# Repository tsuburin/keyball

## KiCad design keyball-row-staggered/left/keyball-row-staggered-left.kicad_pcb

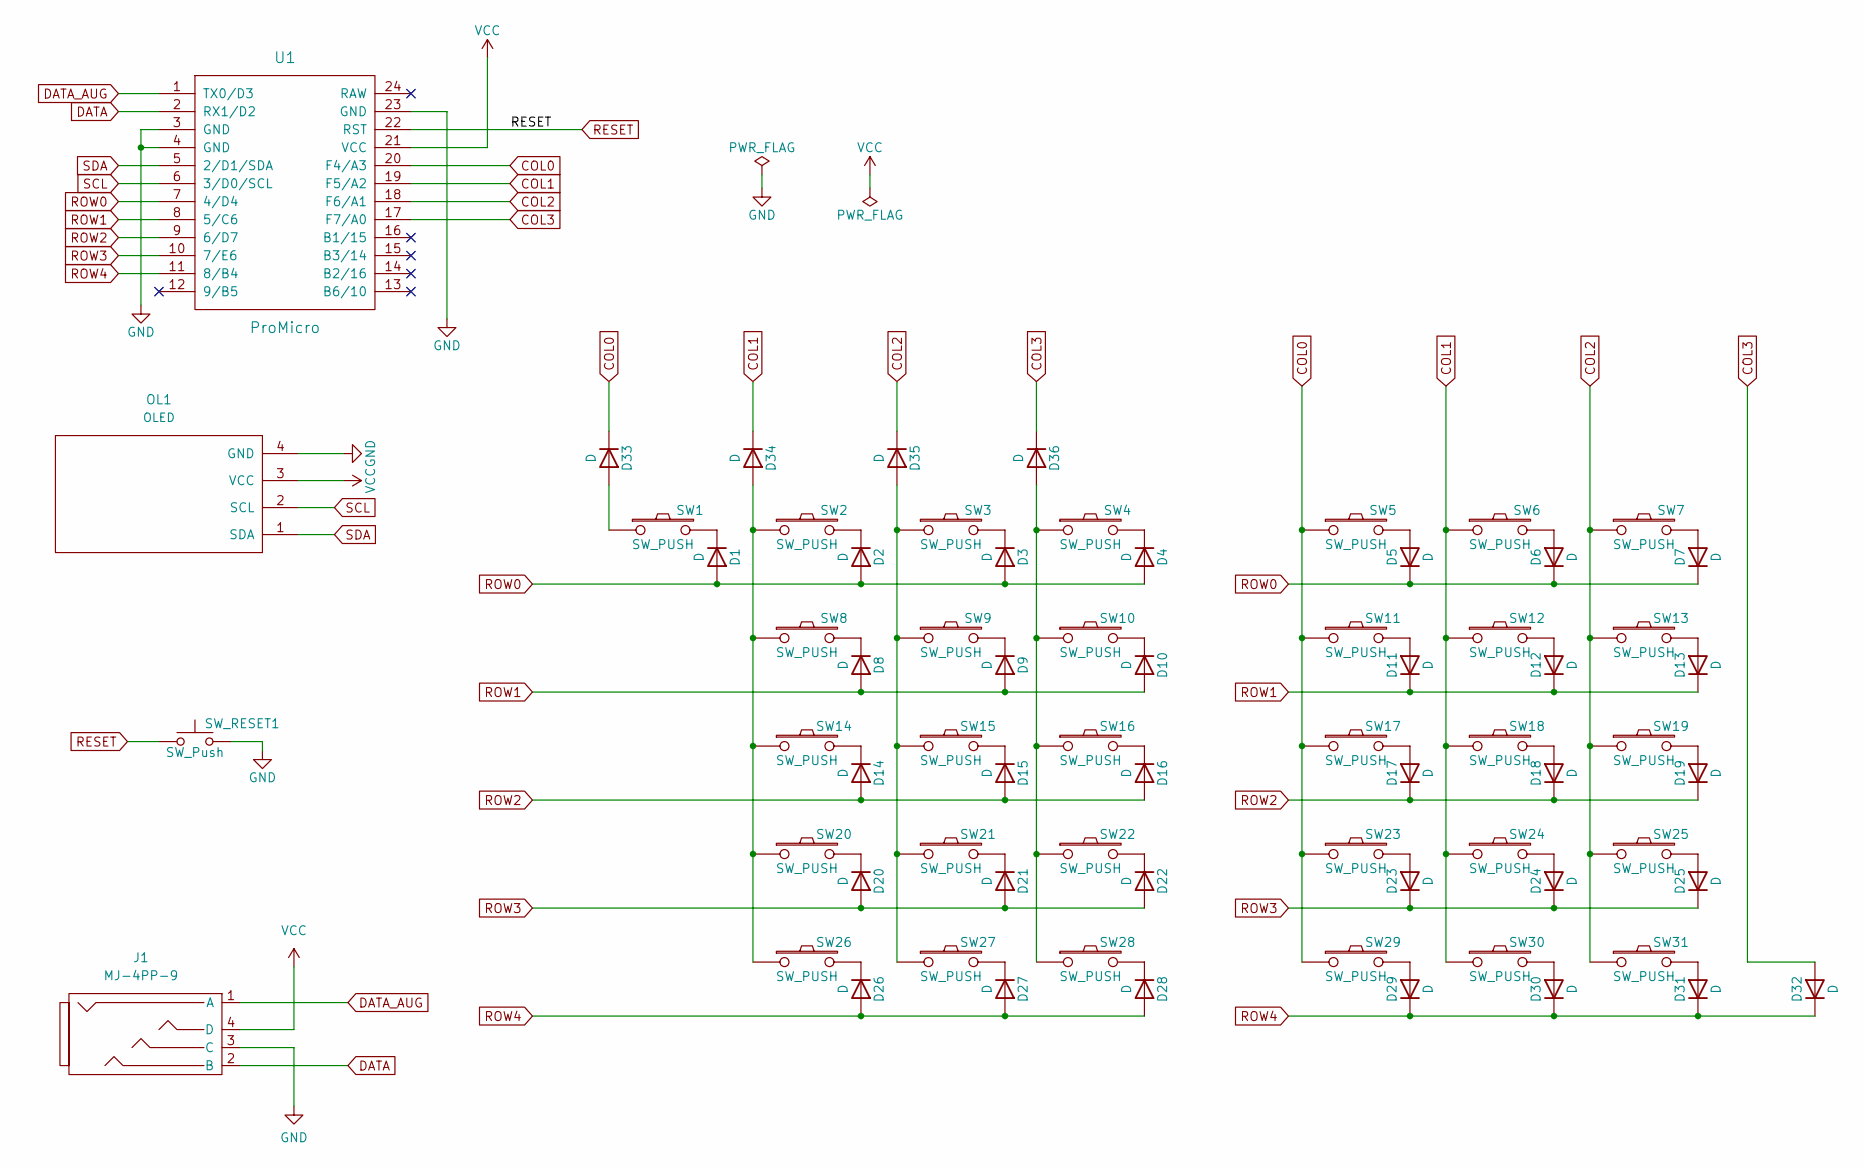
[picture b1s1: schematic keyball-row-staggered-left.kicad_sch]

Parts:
D1, D2, D3, D4, D5, D6, D7, D8, D9, D10, D11, D12, D13, D14, D15, D16, D17, D18, D19, D20, D21, D22, D23, D24, D25, D26, D27, D28, D29, D30, D31, D32, D33, D34, D35, D36: D; D3_SMD_v2
J1: MJ-4PP-9
OL1: OLED; OLED_v2
SW1, SW2, SW3, SW4, SW5, SW6, SW7, SW8, SW9, SW10, SW11, SW12, SW13, SW14, SW15, SW16, SW17, SW18, SW19, SW20, SW21, SW22, SW23, SW24, SW25, SW26, SW27, SW28: SW_PUSH; Kailh_socket_MX
SW29, SW30, SW31: SW_PUSH; CherryMX_Choc_Hotswap
SW_RESET1: SW_Push; ResetSW_1side
U1: ProMicro; ProMicro_v3

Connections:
COL0: D33.1 (K), SW5.1, SW11.1, SW17.1, SW23.1, SW29.1, U1.20 (F4/A3)
COL1: D34.1 (K), SW6.1, SW12.1, SW18.1, SW24.1, SW30.1, U1.19 (F5/A2)
COL2: D35.1 (K), SW7.1, SW13.1, SW19.1, SW25.1, SW31.1, U1.18 (F6/A1)
COL3: D32.2 (A), D36.1 (K), U1.17 (F7/A0)
DATA: J1.2 (B), U1.2 (RX1/D2)
DATA_AUG: J1.1 (A), U1.1 (TX0/D3)
GND: J1.3 (C), OL1.4 (GND), SW_RESET1.2, U1.3 (GND), U1.4 (GND), U1.23 (GND)
unnamed: D1.1 (K), SW1.2
unnamed: D2.1 (K), SW2.2
unnamed: D3.1 (K), SW3.2
unnamed: D4.1 (K), SW4.2
unnamed: D5.2 (A), SW5.2
unnamed: D6.2 (A), SW6.2
unnamed: D7.2 (A), SW7.2
unnamed: D8.1 (K), SW8.2
unnamed: D9.1 (K), SW9.2
unnamed: D10.1 (K), SW10.2
unnamed: D11.2 (A), SW11.2
unnamed: D12.2 (A), SW12.2
unnamed: D13.2 (A), SW13.2
unnamed: D14.1 (K), SW14.2
unnamed: D15.1 (K), SW15.2
unnamed: D16.1 (K), SW16.2
unnamed: D17.2 (A), SW17.2
unnamed: D18.2 (A), SW18.2
unnamed: D19.2 (A), SW19.2
unnamed: D20.1 (K), SW20.2
unnamed: D21.1 (K), SW21.2
unnamed: D22.1 (K), SW22.2
unnamed: D23.2 (A), SW23.2
unnamed: D24.2 (A), SW24.2
unnamed: D25.2 (A), SW25.2
unnamed: D26.1 (K), SW26.2
unnamed: D27.1 (K), SW27.2
unnamed: D28.1 (K), SW28.2
unnamed: D29.2 (A), SW29.2
unnamed: D30.2 (A), SW30.2
unnamed: D31.2 (A), SW31.2
unnamed: D33.2 (A), SW1.1
unnamed: D34.2 (A), SW2.1, SW8.1, SW14.1, SW20.1, SW26.1
unnamed: D35.2 (A), SW3.1, SW9.1, SW15.1, SW21.1, SW27.1
unnamed: D36.2 (A), SW4.1, SW10.1, SW16.1, SW22.1, SW28.1
RESET: SW_RESET1.1, U1.22 (RST)
ROW0: D1.2 (A), D2.2 (A), D3.2 (A), D4.2 (A), D5.1 (K), D6.1 (K), D7.1 (K), U1.7 (4/D4)
ROW1: D8.2 (A), D9.2 (A), D10.2 (A), D11.1 (K), D12.1 (K), D13.1 (K), U1.8 (5/C6)
ROW2: D14.2 (A), D15.2 (A), D16.2 (A), D17.1 (K), D18.1 (K), D19.1 (K), U1.9 (6/D7)
ROW3: D20.2 (A), D21.2 (A), D22.2 (A), D23.1 (K), D24.1 (K), D25.1 (K), U1.10 (7/E6)
ROW4: D26.2 (A), D27.2 (A), D28.2 (A), D29.1 (K), D30.1 (K), D31.1 (K), D32.1 (K), U1.11 (8/B4)
SCL: OL1.2 (SCL), U1.6 (3/D0/SCL)
SDA: OL1.1 (SDA), U1.5 (2/D1/SDA)
VCC: J1.4 (D), OL1.3 (VCC), U1.21 (VCC)

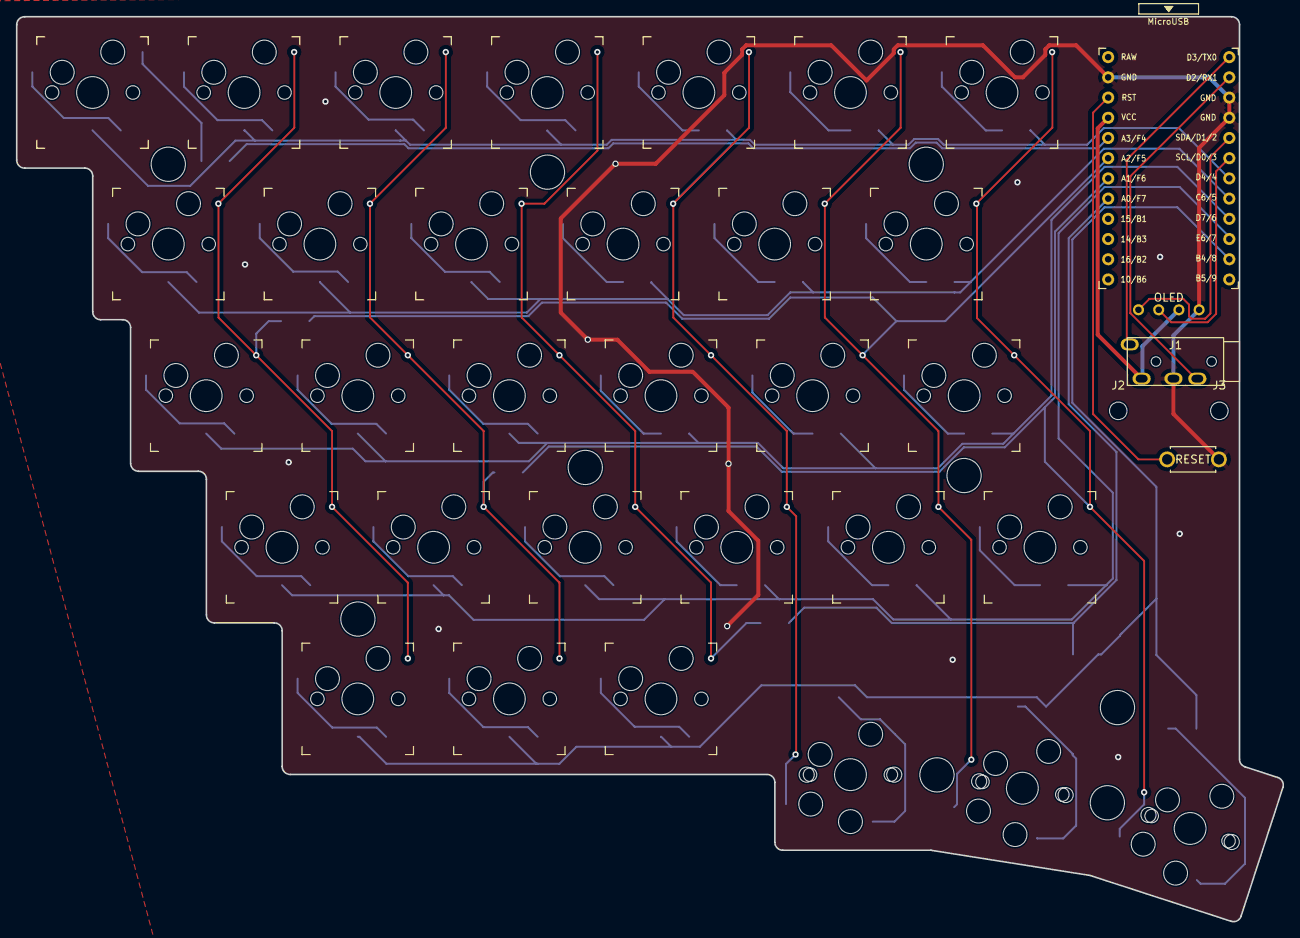
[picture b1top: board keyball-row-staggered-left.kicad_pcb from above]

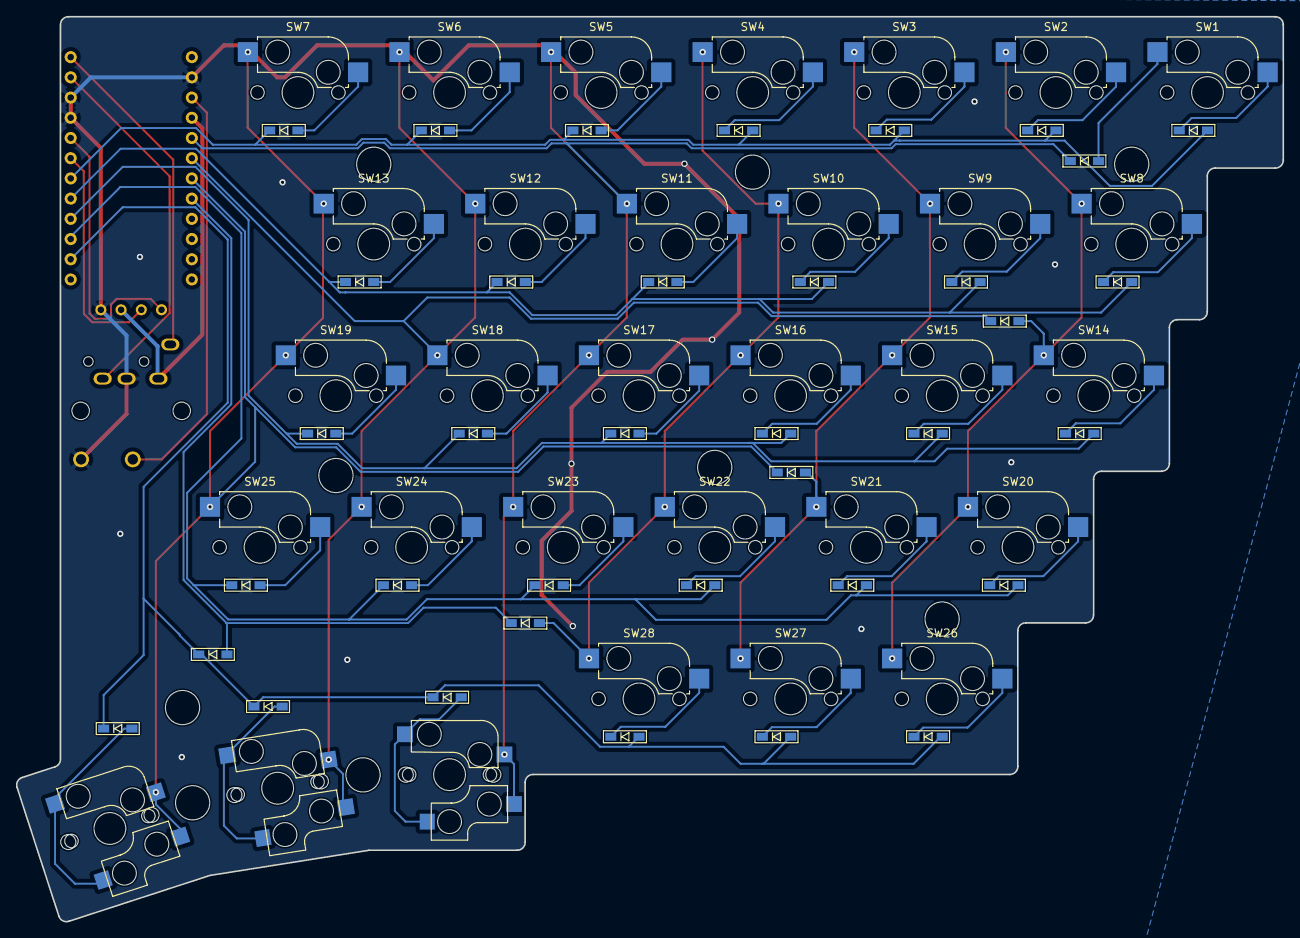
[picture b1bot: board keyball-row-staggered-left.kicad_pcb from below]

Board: 2 copper layers, 159.2 x 113.7 mm, 82 parts (36 on the bottom side), 51 nets.

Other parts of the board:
J2, J3: Conn_01x01_Pin; MountingHole_2.2mm_M2
J4, J5, J6, J7, J8, J9, J10, J11, J12: Conn_01x01_Pin; spacer_m2

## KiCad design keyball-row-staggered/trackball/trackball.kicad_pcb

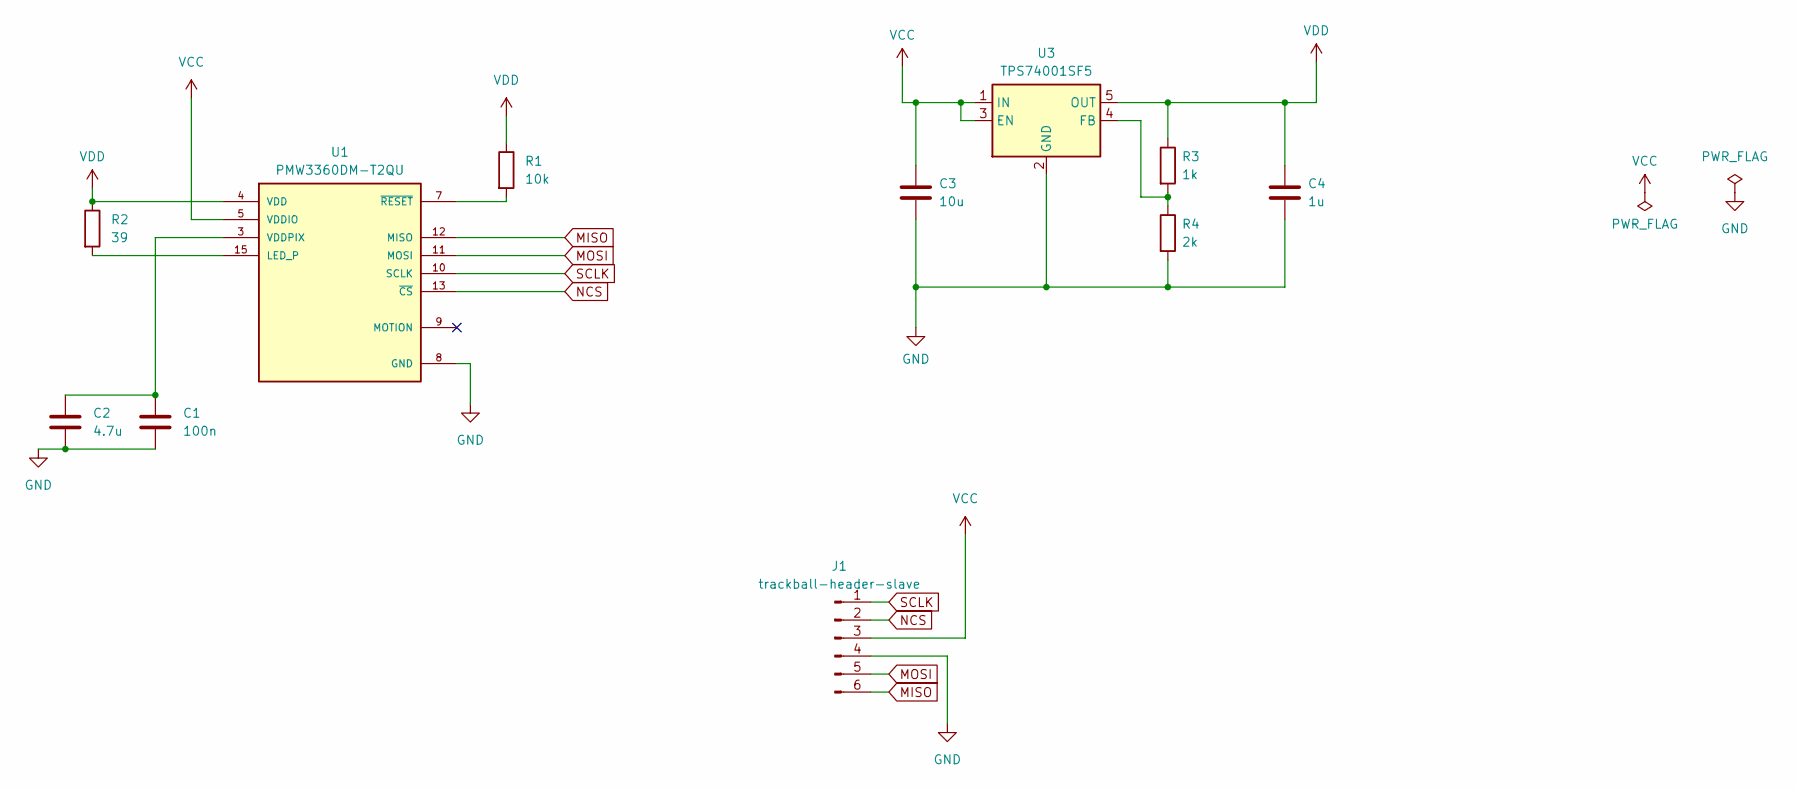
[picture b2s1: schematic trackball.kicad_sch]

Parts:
C1: 100n; C_0603_1608Metric_Pad1.08x0.95mm_HandSolder
C2: 4.7u; C_0603_1608Metric_Pad1.08x0.95mm_HandSolder
C3: 10u; C_0603_1608Metric_Pad1.08x0.95mm_HandSolder
C4: 1u; C_0603_1608Metric_Pad1.08x0.95mm_HandSolder
J1: trackball-header-slave; keyball_trackball_header_slave
R1: 10k; R_0603_1608Metric_Pad0.98x0.95mm_HandSolder
R2: 39; R_0603_1608Metric_Pad0.98x0.95mm_HandSolder
R3: 1k; R_0603_1608Metric_Pad0.98x0.95mm_HandSolder
R4: 2k; R_0603_1608Metric_Pad0.98x0.95mm_HandSolder
U1: PMW3360DM-T2QU; PMW3360
U3: TPS74001SF5; SOT-23-5

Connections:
GND: C1.2, C2.2, C3.2, C4.2, J1.4 (GND), R4.2, U1.8 (GND), U3.2 (GND)
MISO: J1.6 (MISO), U1.12 (MISO)
MOSI: J1.5 (MOSI), U1.11 (MOSI)
NCS: J1.2 (NCS), U1.13 (~CS)
unnamed: R2.2, U1.15 (LED_P)
unnamed: C1.1, C2.1, U1.3 (VDDPIX)
unnamed: R1.2, U1.7 (~RESET)
unnamed: R3.2, R4.1, U3.4 (FB)
SCLK: J1.1 (SCLK), U1.10 (SCLK)
VCC: C3.1, J1.3 (VCC), U1.5 (VDDIO), U3.1 (IN), U3.3 (EN)
VDD: C4.1, R1.1, R2.1, R3.1, U1.4 (VDD), U3.5 (OUT)

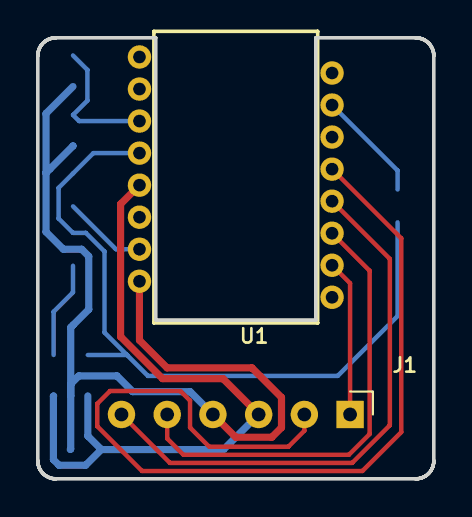
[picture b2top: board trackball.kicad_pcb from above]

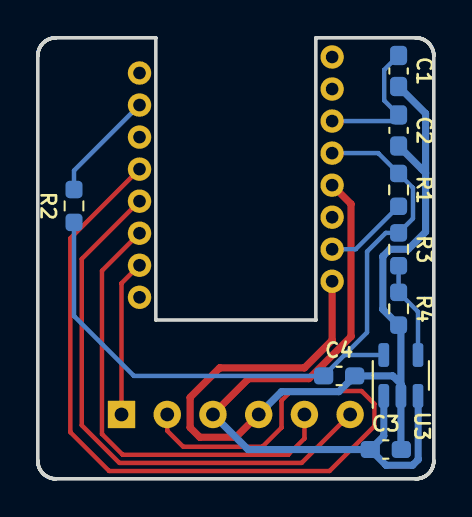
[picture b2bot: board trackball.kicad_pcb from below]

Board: 2 copper layers, 22.0 x 24.5 mm, 11 parts (9 on the bottom side), 11 nets.

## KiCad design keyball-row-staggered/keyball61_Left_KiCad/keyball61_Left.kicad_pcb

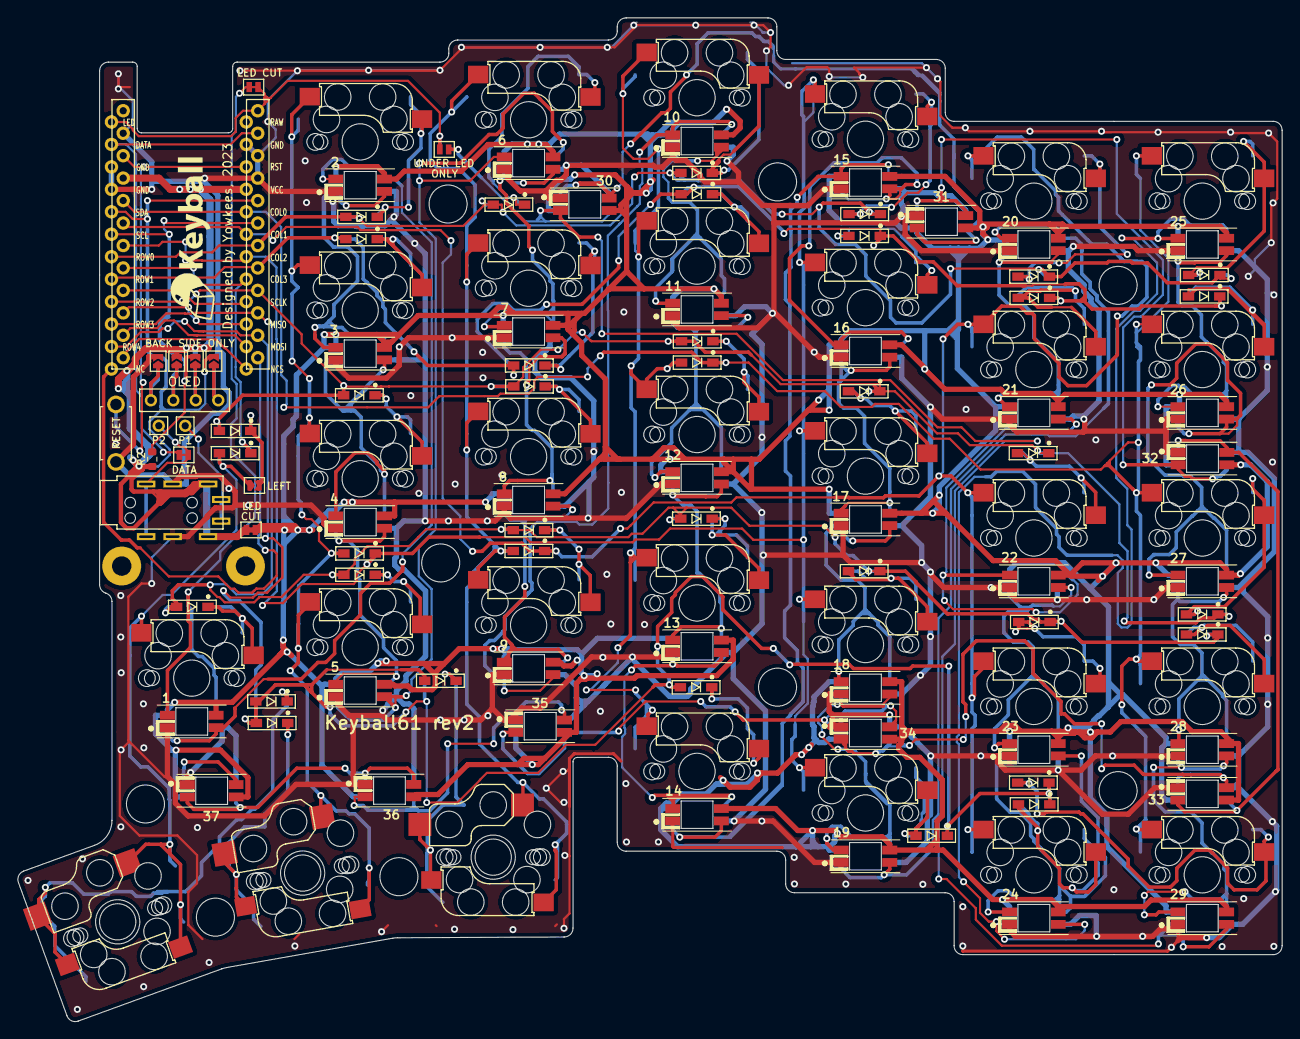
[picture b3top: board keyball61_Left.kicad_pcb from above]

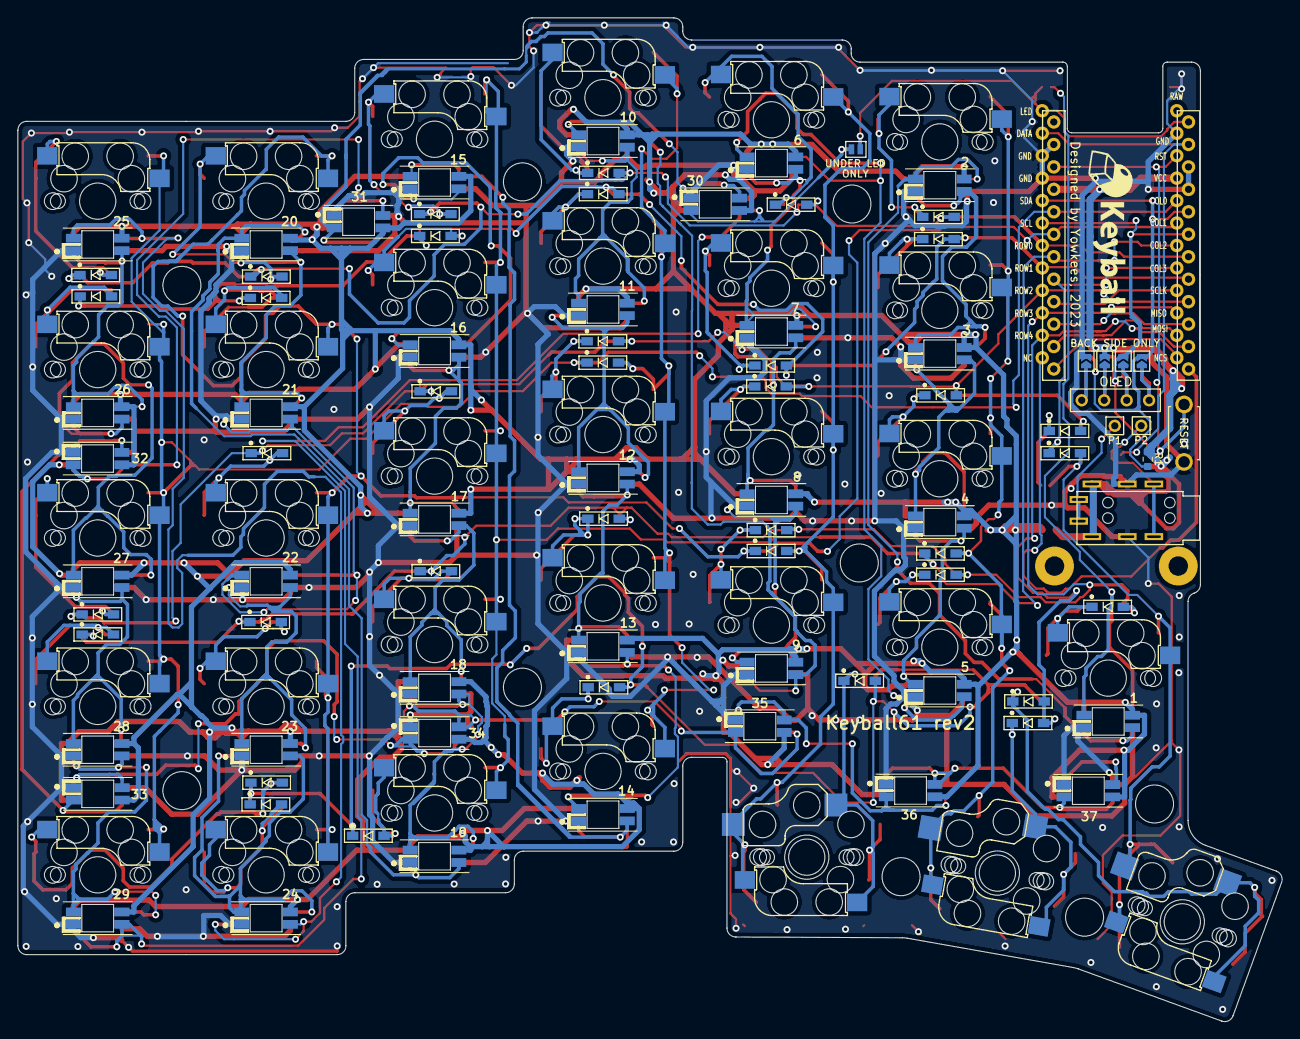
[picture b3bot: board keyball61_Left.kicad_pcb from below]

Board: 2 copper layers, 142.9 x 113.5 mm, 139 parts (6 on the bottom side), 97 nets.

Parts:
1, 2, 3, 4, 5, 6, 7, 8, 9, 10, 11, 12, 13, 14, 15, 16, 17, 18, 19, 20, 21, 22, 23, 24, 25, 26, 27, 28, 29: YS-SK6812MINI-E; YS-SK6812MINI-Keyball-TL
30, 31, 32, 33, 34, 35, 36, 37: YS-SK6812MINI-E; YS-SK6812MINI-Keyball-BL
D1, D2, D3, D4, D5, D6, D7, D8, D9, D10, D11, D12, D13, D14, D15, D16, D17, D18, D19, D20, D21, D22, D23, D24, D25, D26, D27, D28, D29, D30, D31, D32, D33, D34, D35, D36, D37: D; D3_SMD_v2_BOTH
DATA: Device_Jumper; JP025
J1: OLED
J2, J3: Conn_01x01-Connector_Generic; MountingHole_2.2mm_M2_Pad
J4, J5, J6, J7, J8, J9, J10, J11, J12: Conn_01x01-Connector_Generic; MountingHole_4.3mm_M4
J13: TRS_JACK; TRRS_JACK_MJ4PP9
JP1: LEFT; Jumper_NEW
JP2, JP3, JP4, JP6, JP8, JP9: Device_Jumper_NO_Small; Jumper_NEW
JP5, JP7: BACK SIDE ONLY; Jumper_NEW
JP13, JP14: UNDER LED; Jumper
LED: CUT; JP06
LED CUT: Device_Jumper_NO_Small; JP025
P1, P2: I2C; 1pin_conn
R1, R2: PULL_UP; R_0603_1608Metric
SW1, SW2, SW3, SW4, SW5, SW6, SW7, SW8, SW9, SW10, SW11, SW12, SW13, SW14, SW15, SW16, SW17, SW18, SW19, SW20, SW21, SW22, SW23, SW24, SW25, SW26, SW27, SW28, SW29: SW_PUSH-kbd; CherryMX_MidHeight_Hotswap
SW30, SW31, SW32: SW_PUSH-kbd; MX&Choc_V1_V2_Hotswap_BOTH
SW33: RESET_SW; ResetSW
U1: ProMicro-kbd; ProMicro_v2_for61

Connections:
COL0: D34.1, SW1.1, SW7.1, SW13.1, SW19.1, SW26.1, U1.20
COL1: D35.1, SW2.1, SW8.1, SW14.1, SW20.1, SW27.1, U1.19
COL2: D36.1, SW3.1, SW9.1, SW15.1, SW21.1, SW28.1, U1.18
COL3: D37.1, U1.17
DATA: DATA.2, U1.2
GND: 1.3, 2.3, 3.3, 4.3, 5.3, 6.3, 7.3, 8.3, 9.3, 10.3, 11.3, 12.3, 13.3, 14.3, 15.3, 16.3, 17.3, 18.3, 19.3, 20.3, 21.3, 22.3, 23.3, 24.3, 25.3, 26.3, 27.3, 28.3, 29.3, 30.3, 31.3, 32.3, 33.3, 34.3, 35.3, 36.3, 37.3, J13.C, JP2.2, JP9.2, SW33.2, U1.3, U1.4, U1.23
LED: JP13.2, JP14.2, LED CUT.1, U1.1
unnamed: D1.2, SW1.2
unnamed: D2.2, SW2.2
unnamed: D3.2, SW3.2
unnamed: D4.1, SW4.2
unnamed: D5.1, SW5.2
unnamed: D6.1, SW6.2
unnamed: D7.2, SW7.2
unnamed: D8.2, SW8.2
unnamed: D9.2, SW9.2
unnamed: D10.1, SW10.2
unnamed: D11.1, SW11.2
unnamed: D12.1, SW12.2
unnamed: D13.2, SW13.2
unnamed: D14.2, SW14.2
unnamed: D15.2, SW15.2
unnamed: D16.1, SW16.2
unnamed: D17.1, SW17.2
unnamed: D18.1, SW18.2
unnamed: D19.1, JP1.2
unnamed: D20.2, SW19.2
unnamed: D21.2, SW20.2
unnamed: D22.2, SW21.2
unnamed: D23.1, SW22.2
unnamed: D24.1, SW23.2
unnamed: D25.1, SW24.2
unnamed: D26.1, SW25.2
unnamed: D27.2, SW26.2
unnamed: D28.2, SW27.2
unnamed: D29.2, SW28.2
unnamed: D30.1, SW29.2
unnamed: D31.1, SW30.2
unnamed: D32.1, SW31.2
unnamed: D33.1, SW32.2
unnamed: D34.2, SW4.1, SW10.1, SW16.1, SW22.1, SW29.1
unnamed: D35.2, SW5.1, SW11.1, SW17.1, SW23.1, SW30.1
unnamed: D36.2, SW6.1, SW12.1, SW18.1, SW24.1, SW31.1
unnamed: D37.2, JP1.1, SW25.1, SW32.1
unnamed: J1.1, JP2.1, JP6.1
unnamed: J1.2, JP3.1, JP7.1
unnamed: J1.3, JP4.1, JP8.1
unnamed: J1.4, JP5.1, JP9.1
unnamed: J13.A, P1.1
unnamed: DATA.1, J13.B, P2.1
unnamed: 1.1, 2.1, 3.1, 4.1, 5.1, 6.1, 7.1, 8.1, 9.1, 10.1, 11.1, 12.1, 13.1, 14.1, 15.1, 16.1, 17.1, 18.1, 19.1, 20.1, 21.1, 22.1, 23.1, 24.1, 25.1, 26.1, 27.1, 28.1, 29.1, 30.1, 31.1, 32.1, 33.1, 34.1, 35.1, 36.1, 37.1, LED.1
unnamed: 1.4, LED CUT.2
unnamed: 29.2, 30.4, JP13.1, JP14.1
unnamed: 1.2, 2.4
unnamed: 2.2, 3.4
unnamed: 3.2, 4.4
unnamed: 4.2, 5.4
unnamed: 5.2, 6.4
unnamed: 6.2, 7.4
unnamed: 7.2, 8.4
unnamed: 8.2, 9.4
unnamed: 10.2, 11.4
unnamed: 9.2, 10.4
unnamed: 11.2, 12.4
unnamed: 12.2, 13.4
unnamed: 13.2, 14.4
unnamed: 14.2, 15.4
unnamed: 15.2, 16.4
unnamed: 16.2, 17.4
unnamed: 17.2, 18.4
unnamed: 18.2, 19.4
unnamed: 19.2, 20.4
unnamed: 20.2, 21.4
unnamed: 21.2, 22.4
unnamed: 22.2, 23.4
unnamed: 23.2, 24.4
unnamed: 24.2, 25.4
unnamed: 25.2, 26.4
unnamed: 26.2, 27.4
unnamed: 27.2, 28.4
unnamed: 28.2, 29.4
unnamed: 30.2, 31.4
unnamed: 31.2, 32.4
unnamed: 32.2, 33.4
unnamed: 33.2, 34.4
unnamed: 34.2, 35.4
unnamed: 35.2, 36.4
unnamed: 36.2, 37.4
RESET: SW33.1, U1.22
ROW0: D1.1, D2.1, D3.1, D4.2, D5.2, D6.2, U1.7
ROW1: D7.1, D8.1, D9.1, D10.2, D11.2, D12.2, U1.8
ROW2: D13.1, D14.1, D15.1, D16.2, D17.2, D18.2, D19.2, U1.9
ROW3: D20.1, D21.1, D22.1, D23.2, D24.2, D25.2, D26.2, U1.10
ROW4: D27.1, D28.1, D29.1, D30.2, D31.2, D32.2, D33.2, U1.11
SCL: JP4.2, JP7.2, R2.2, U1.6
SDA: JP5.2, JP6.2, R1.2, U1.5
VCC: J13.D, JP3.2, JP8.2, LED.2, R1.1, R2.1, U1.21

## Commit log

2024-02-07 prolong SPLIT_USB_TIMEOUT
2024-02-08 enable auto mouse layer
2024-02-15 回路図（未ベタ）
2024-02-16 add order-number placeholder
2024-02-16 右手配置修正
2024-02-16 ドリル原点設定
2024-02-17 trackball基板追加
2024-02-17 backupファイルをgitから削除
2024-02-18 キーボード側をtrackball基板に合わせて修正
2024-02-18 backupファイル削除
2024-02-18 topプレート作成
2024-02-18 bottomプレート作成
2024-02-18 middleプレート作成
2024-02-18 アクリル発注データ作成
2024-02-19 add gitignore
2024-02-19 nenecchi追加
2024-02-19 firmware作成
2024-02-19 発注ファイル作成
2024-02-19 不要なスクリプト削除
2025-04-17 elecrow発注ファイル
2025-04-17 images
